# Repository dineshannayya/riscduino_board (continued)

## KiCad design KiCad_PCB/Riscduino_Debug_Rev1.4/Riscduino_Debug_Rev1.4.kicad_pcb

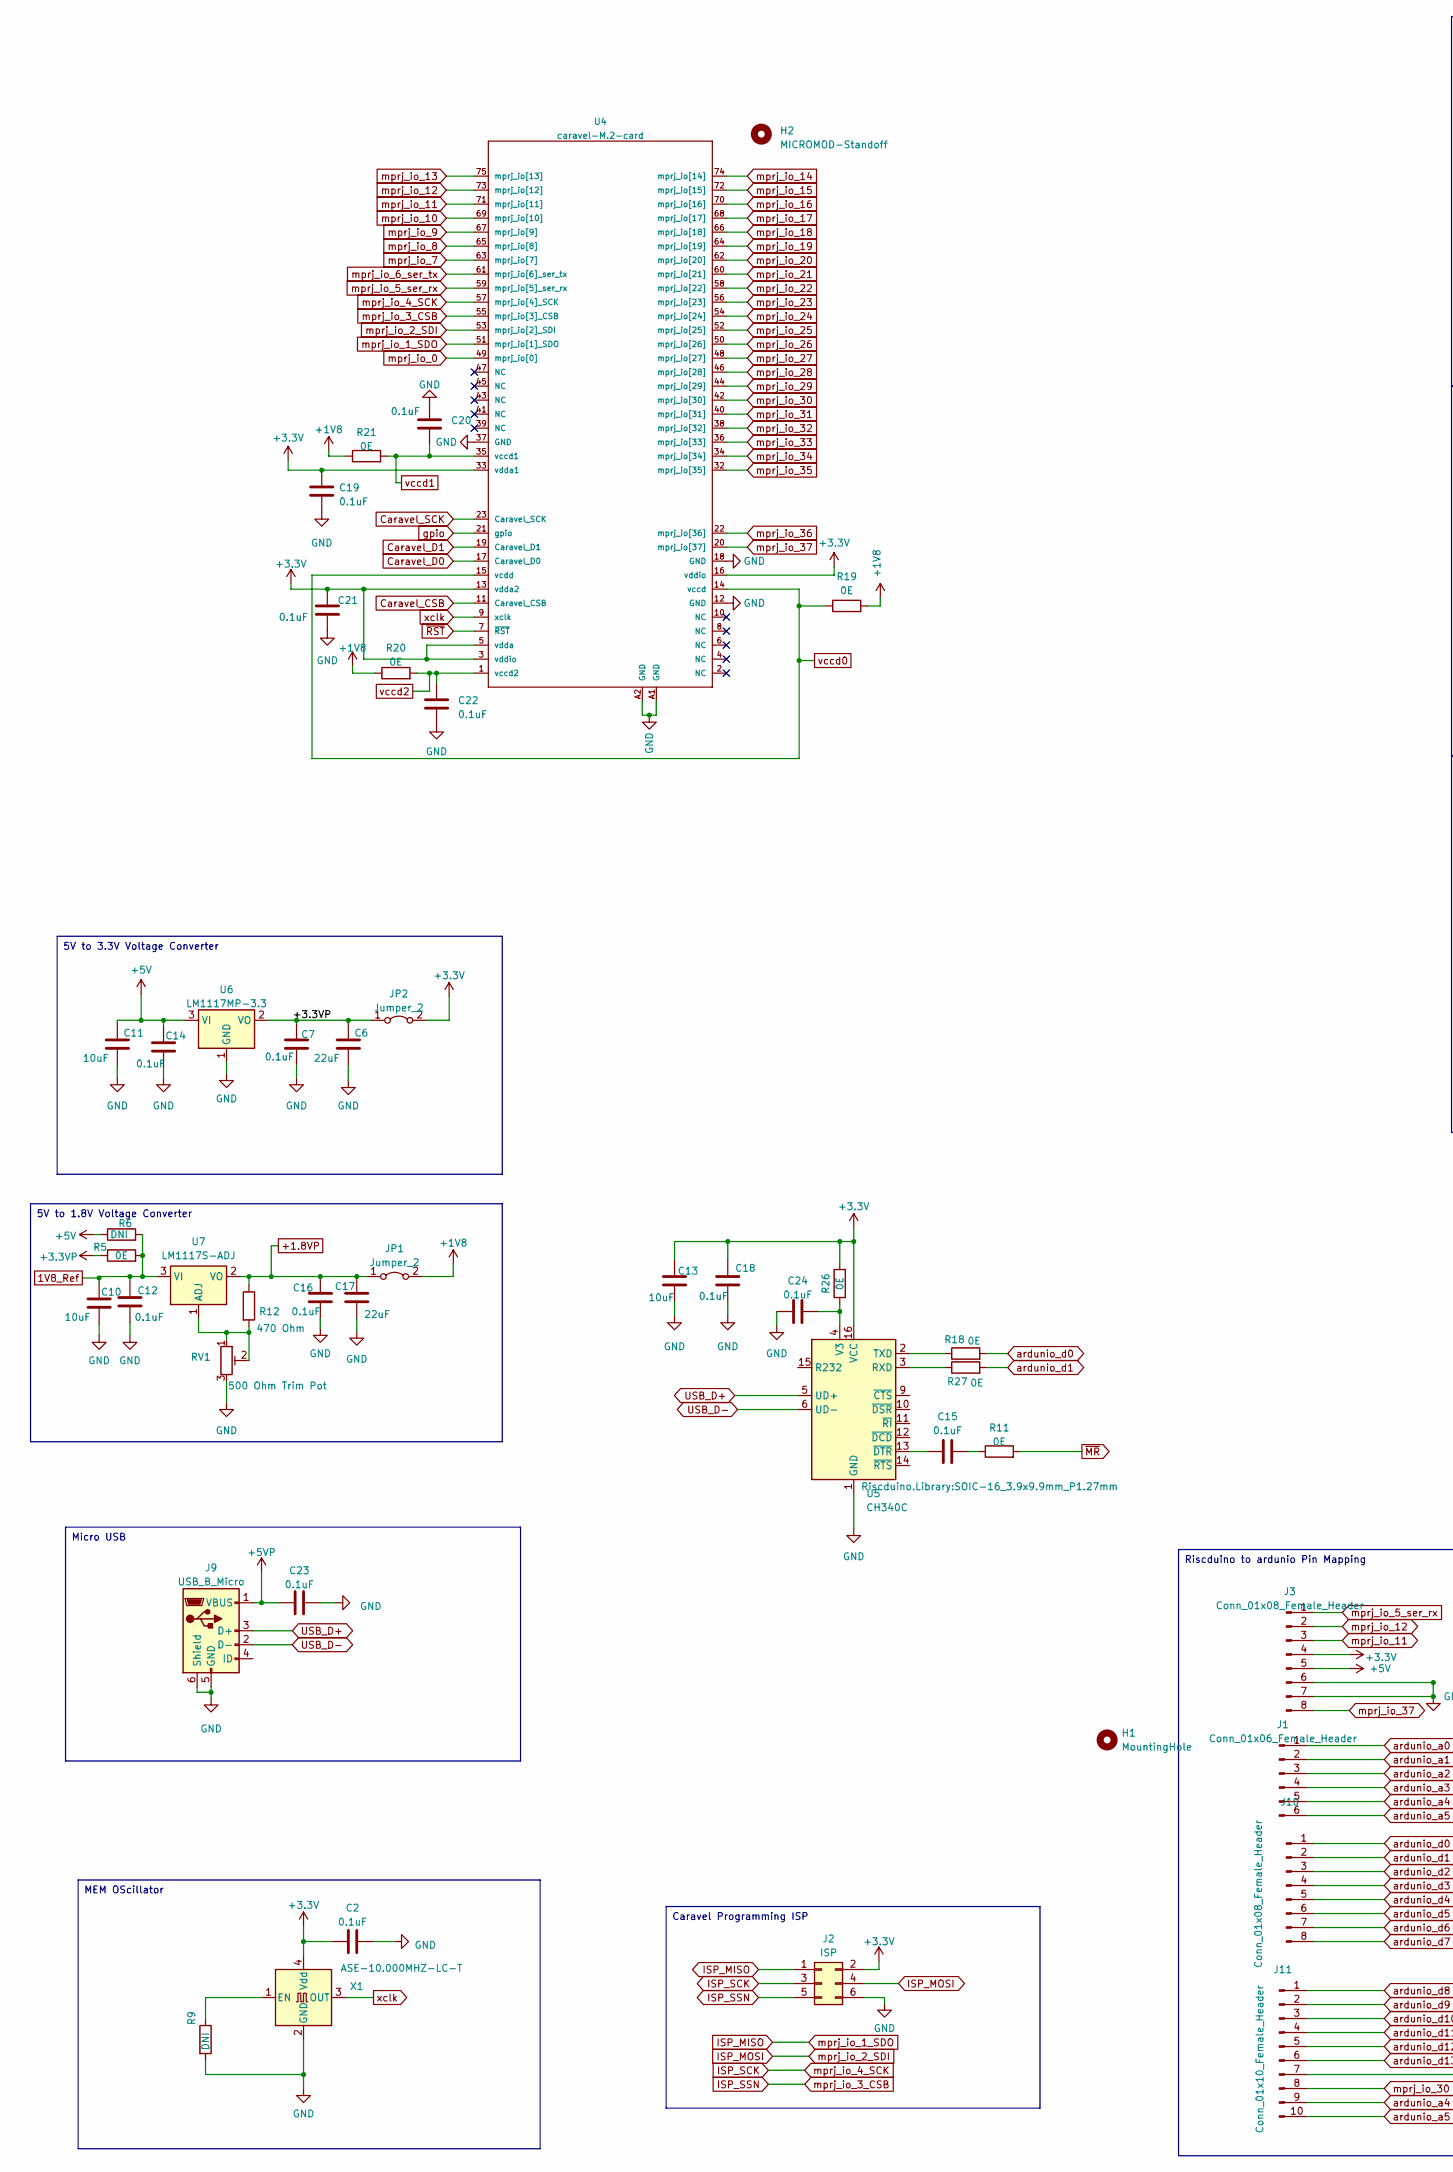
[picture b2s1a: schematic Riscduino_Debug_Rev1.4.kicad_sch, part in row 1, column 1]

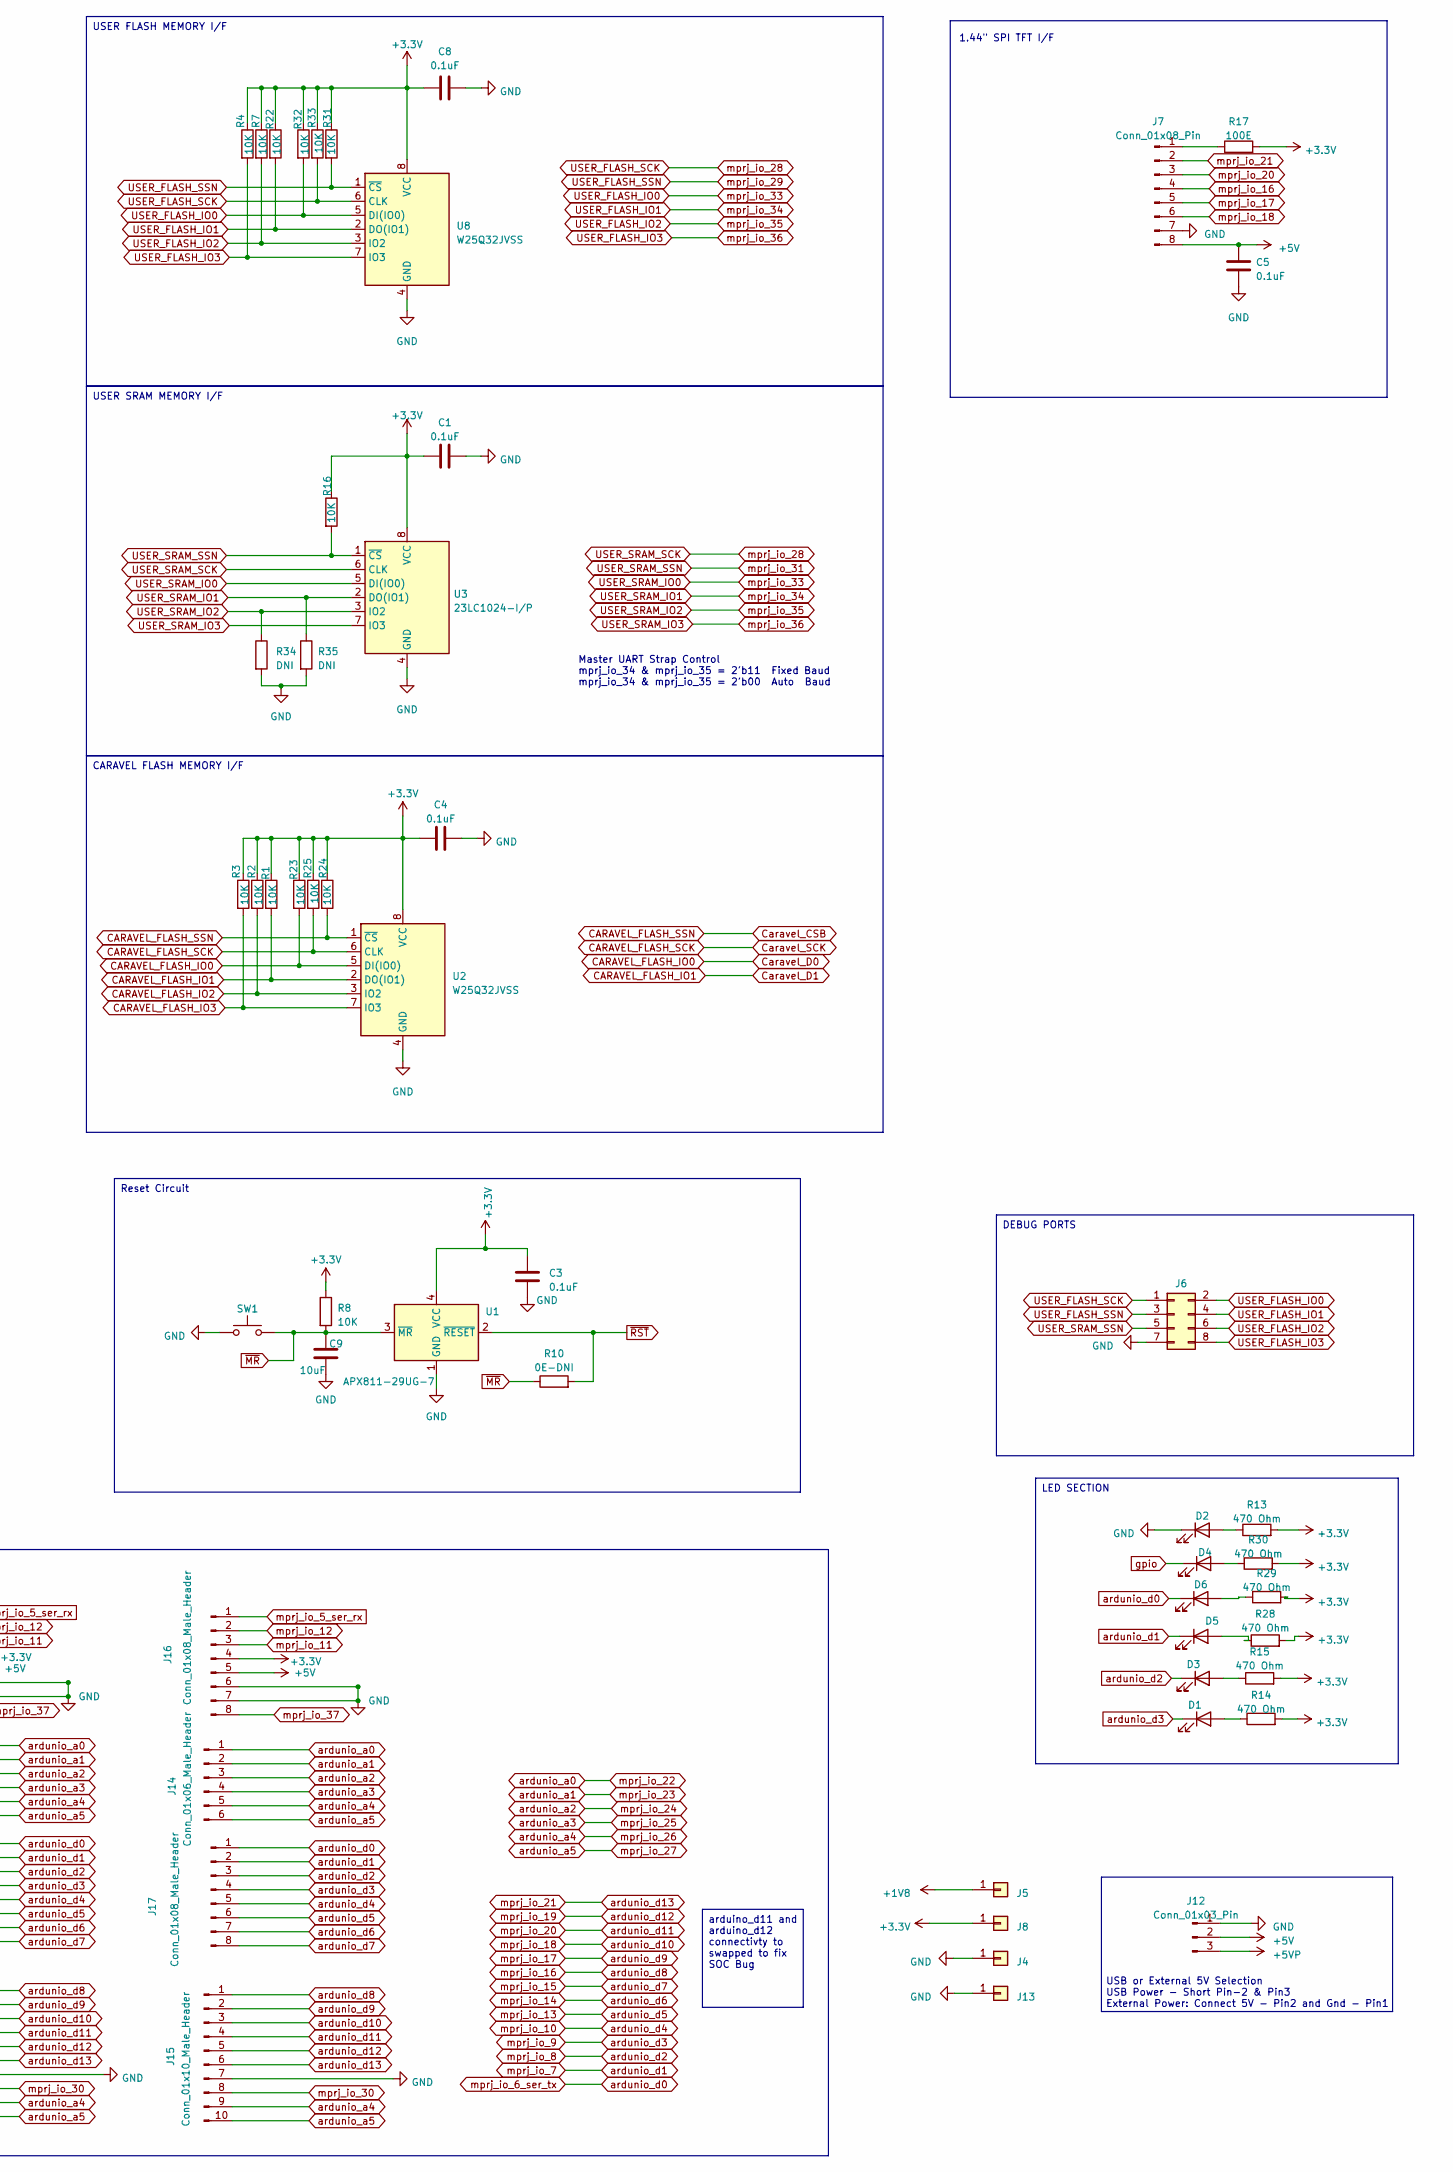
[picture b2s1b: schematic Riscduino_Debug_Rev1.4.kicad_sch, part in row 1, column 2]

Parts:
C1, C2, C3, C4, C5, C7, C8, C12, C14, C15, C16, C18, C19, C20, C21, C22, C23, C24: 0.1uF; C_0603_1608Metric_Pad1.08x0.95mm_HandSolder
C6, C17: 22uF; C_0805_2012Metric_Pad1.18x1.45mm_HandSolder
C9, C10, C11, C13: 10uF; C_0805_2012Metric_Pad1.18x1.45mm_HandSolder
D1, D2, D3, D4, D5: GREEN LED; LED_0805_2012Metric_Pad1.15x1.40mm_HandSolder
D6: BLUE LED; LED_0805_2012Metric_Pad1.15x1.40mm_HandSolder
H1: MountingHole; Arduino_UNO_R3_WithMountingHoles
H2: MICROMOD-Standoff; MicroMod-Standoff
J1: Conn_01x06_Female_Header; PinHeader_1x06_P2.54mm_Vertical
J2: ISP; PinHeader_2x03_P2.54mm_Vertical
J3, J10: Conn_01x08_Female_Header; PinHeader_1x08_P2.54mm_Vertical
J4, J5, J8, J13: Conn_01x01; PinHeader_1x01_P2.54mm_Vertical
J6: Conn_02x04_Odd_Even; PinHeader_2x04_P2.54mm_Vertical
J7: Conn_01x08_Pin; PinHeader_1x08_P2.54mm_Vertical
J9: USB_B_Micro; USB_Micro-B_Molex-105017-0001
J11: Conn_01x10_Female_Header; PinHeader_1x10_P2.54mm_Vertical
J12: Conn_01x03_Pin; PinHeader_1x03_P2.54mm_Vertical
J14: Conn_01x06_Male_Header; PinHeader_1x06_P2.54mm_Vertical
J15: Conn_01x10_Male_Header; PinHeader_1x10_P2.54mm_Vertical
J16, J17: Conn_01x08_Male_Header; PinHeader_1x08_P2.54mm_Vertical
JP1, JP2: Jumper_2; PinHeader_1x02_P2.54mm_Vertical
R1, R2, R3, R4, R7, R8, R16, R22, R23, R24, R25, R31, R32, R33: 10K; R_0603_1608Metric_Pad0.98x0.95mm_HandSolder
R5, R11, R18, R19, R20, R21, R26, R27: 0E; R_0603_1608Metric_Pad0.98x0.95mm_HandSolder
R6, R9, R34, R35: DNI; R_0603_1608Metric_Pad0.98x0.95mm_HandSolder
R10: 0E-DNI; C_0603_1608Metric_Pad1.08x0.95mm_HandSolder
R12, R13, R14, R15, R28, R29, R30: 470 Ohm; R_0603_1608Metric_Pad0.98x0.95mm_HandSolder
R17: 100E; R_0603_1608Metric_Pad0.98x0.95mm_HandSolder
RV1: 500 Ohm Trim Pot; Potentiometer_Bourns_3296W_Vertical
SW1: 4Pin Round Button SPST Straight Tactile Switch SM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; SW_SPST_EVPBF_TS4550TP
U1: APX811-29UG-7; SOT-143_Handsoldering
U2, U8: W25Q32JVSS; SOIC-8_5.23x5.23mm_P1.27mm
U3: 23LC1024-I/P; DIP-8_W7.62mm_LongPads
U4: caravel-M.2-card; M.2-CONNECTOR-E
U5: CH340C; SOIC-16_3.9x9.9mm_P1.27mm
U6: LM1117MP-3.3; SOT-223-3_TabPin2
U7: LM1117S-ADJ; SOT-223-3_TabPin2
X1: ASE-10.000MHZ-LC-T; Crystal_SMD_Abracon_ABM8G-4Pin_3.2x2.5mm

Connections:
1V8_Ref: C10.1, C12.1, R5.2, R6.2, U7.3 (VI)
+1.8VP: C16.1, C17.1, JP1.1 (A), R12.1, U7.2 (VO)
+1V8: J5.1, JP1.2 (B), R19.2, R20.1, R21.1
+3.3V: C1.1, C2.1, C3.1, C4.1, C8.1, C13.1, C18.1, C19.1, C21.1, J2.2, J3.4, J8.1, J16.4, JP2.2 (B), R1.1, R2.1, R3.1, R4.1, R7.1, R8.1, R13.2, R14.2, R15.2, R16.1, R17.2, R22.1, R23.1, R24.1, R25.1, R26.2, R28.2, R29.2, R30.2, R31.1, R32.1, R33.1, U1.4 (VCC), U2.8 (VCC), U3.8 (VCC), U4.3 (vddio), U4.5 (vdda), U4.13 (vdda2), U4.16 (vddio), U4.33 (vdda1), U5.16 (VCC), U8.8 (VCC), X1.4 (Vdd)
+3.3VP: C6.1, C7.1, JP2.1 (A), R5.1, U6.2 (VO)
+5V: C5.1, C11.1, C14.1, J3.5, J7.8, J12.2, J16.5, R6.1, U6.3 (VI)
+5VP: C23.1, J9.1 (VBUS), J12.3
CARAVEL_FLASH_IO0: R23.2, U2.5 (DI(IO0)), U4.17 (Caravel_D0)
CARAVEL_FLASH_IO1: R1.2, U2.2 (DO(IO1)), U4.19 (Caravel_D1)
CARAVEL_FLASH_IO2: R2.2, U2.3 (IO2)
CARAVEL_FLASH_IO3: R3.2, U2.7 (IO3)
CARAVEL_FLASH_SCK: R25.2, U2.6 (CLK), U4.23 (Caravel_SCK)
CARAVEL_FLASH_SSN: R24.2, U2.1 (~CS), U4.11 (Caravel_CSB)
GND: C1.2, C2.2, C3.2, C4.2, C5.2, C6.2, C7.2, C8.2, C9.2, C10.2, C11.2, C12.2, C13.2, C14.2, C16.2, C17.2, C18.2, C19.2, C20.1, C21.2, C22.2, C23.2, C24.1, D2.1 (K), J2.6, J3.6, J3.7, J4.1, J6.7, J7.7, J9.5 (GND), J9.6 (Shield), J11.7, J12.1, J13.1, J15.7, J16.6, J16.7, R9.2, R34.2, R35.2, RV1.3, SW1.1, U1.1 (GND), U2.4 (GND), U3.4 (GND), U4.12 (GND), U4.18 (GND), U4.37 (GND), U4.A1 (GND), U4.A2 (GND), U5.1 (GND), U6.1 (GND), U8.4 (GND), X1.2 (GND)
ISP_MISO: J2.1, U4.51 (mprj_io[1]_SDO)
ISP_MOSI: J2.4, U4.53 (mprj_io[2]_SDI)
ISP_SCK: J2.3, U4.57 (mprj_io[4]_SCK)
ISP_SSN: J2.5, U4.55 (mprj_io[3]_CSB)
unnamed: C15.2, R11.1
unnamed 19: D1.2 (A), R14.1; also elsewhere on the board
unnamed: D2.2 (A), R13.1
unnamed: D3.2 (A), R15.1
unnamed: D4.2 (A), R30.1
unnamed: D5.2 (A), R28.1
unnamed: D6.2 (A), R29.1
unnamed: J7.1, R17.1
unnamed: R27.1, U5.3 (RXD)
unnamed: R18.1, U5.2 (TXD)
unnamed: C24.2, R26.1, U5.4 (V3)
unnamed: C15.1, U5.13 (~DTR)
unnamed: R12.2, RV1.1, RV1.2, U7.1 (ADJ)
unnamed: R9.1, X1.1 (EN)
USB_D+: J9.3 (D+), U5.5 (UD+)
USB_D-: J9.2 (D-), U5.6 (UD-)
USER_FLASH_IO0: J6.2, R32.2, U3.5 (DI(IO0)), U4.36 (mprj_io[33]), U8.5 (DI(IO0))
USER_FLASH_IO1: J6.4, R22.2, R35.1, U3.2 (DO(IO1)), U4.34 (mprj_io[34]), U8.2 (DO(IO1))
USER_FLASH_IO2: J6.6, R7.2, R34.1, U3.3 (IO2), U4.32 (mprj_io[35]), U8.3 (IO2)
USER_FLASH_IO3: J6.8, R4.2, U3.7 (IO3), U4.22 (mprj_io[36]), U8.7 (IO3)
USER_FLASH_SCK: J6.1, R33.2, U3.6 (CLK), U4.46 (mprj_io[28]), U8.6 (CLK)
USER_FLASH_SSN: J6.3, R31.2, U4.44 (mprj_io[29]), U8.1 (~CS)
USER_SRAM_SSN: J6.5, R16.2, U3.1 (~CS), U4.40 (mprj_io[31])
ardunio_a0: J1.1, J14.1, U4.58 (mprj_io[22])
ardunio_a1: J1.2, J14.2, U4.56 (mprj_io[23])
ardunio_a2: J1.3, J14.3, U4.54 (mprj_io[24])
ardunio_a3: J1.4, J14.4, U4.52 (mprj_io[25])
ardunio_a4: J1.5, J11.9, J14.5, J15.9, U4.50 (mprj_io[26])
ardunio_a5: J1.6, J11.10, J14.6, J15.10, U4.48 (mprj_io[27])
ardunio_d0: D6.1 (K), J10.1, J17.1, R18.2, U4.61 (mprj_io[6]_ser_tx)
ardunio_d1: D5.1 (K), J10.2, J17.2, R27.2, U4.63 (mprj_io[7])
ardunio_d2: D3.1 (K), J10.3, J17.3, U4.65 (mprj_io[8])
ardunio_d3: D1.1 (K), J10.4, J17.4, U4.67 (mprj_io[9]), U8.67; also elsewhere on the board
ardunio_d4: J10.5, J17.5, U4.69 (mprj_io[10])
ardunio_d5: J10.6, J17.6, U4.75 (mprj_io[13])
ardunio_d6: J10.7, J17.7, U4.74 (mprj_io[14])
ardunio_d7: J10.8, J17.8, U4.72 (mprj_io[15])
ardunio_d8: J7.4, J11.1, J15.1, U4.70 (mprj_io[16])
ardunio_d9: J7.5, J11.2, J15.2, U4.68 (mprj_io[17])
ardunio_d10: J7.6, J11.3, J15.3, U4.66 (mprj_io[18])
ardunio_d11: J7.3, J11.4, J15.4, U4.62 (mprj_io[20])
ardunio_d12: J11.5, J15.5, U4.64 (mprj_io[19])
ardunio_d13: J7.2, J11.6, J15.6, U4.60 (mprj_io[21])
gpio: D4.1 (K), U4.21 (gpio)
mprj_io_0: U4.49 (mprj_io[0])
mprj_io_5_ser_rx: J3.1, J16.1, U4.59 (mprj_io[5]_ser_rx)
mprj_io_11: J3.3, J16.3, U4.71 (mprj_io[11])
mprj_io_12: J3.2, J16.2, U4.73 (mprj_io[12])
mprj_io_30: J11.8, J15.8, U4.42 (mprj_io[30])
mprj_io_32: U4.38 (mprj_io[32])
mprj_io_37: J3.8, J16.8, U4.20 (mprj_io[37])
vccd0: R19.1, U4.14 (vccd), U4.15 (vcdd)
vccd1: C20.2, R21.2, U4.35 (vccd1)
vccd2: C22.1, R20.2, U4.1 (vccd2)
xclk: U4.9 (xclk), X1.3 (OUT)
~MR: C9.1, R8.2, R10.1, R11.2, SW1.2, U1.3 (~MR)
~RST: R10.2, U1.2 (~RESET), U4.7 (~RST)

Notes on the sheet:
MEM OScillator
5V to 3.3V Voltage Converter
LED SECTION
Riscduino to ardunio Pin Mapping
Micro USB
arduino_d11 and arduino_d12 connectivty to swapped to fix SOC Bug
USER SRAM MEMORY I/F
DEBUG PORTS
Caravel Programming ISP
USER FLASH MEMORY I/F
5V to 1.8V Voltage Converter
Reset Circuit
CARAVEL FLASH MEMORY I/F
USB or External 5V Selection USB Power - Short Pin-2 & Pin3 External Power: Connect 5V - Pin2 and Gnd - Pin1
1.44" SPI TFT I/F
Master UART Strap Control mprj_io_34 & mprj_io_35 = 2'b11 Fixed Baud mprj_io_34 & mprj_io_35 = 2'b00 Auto Baud

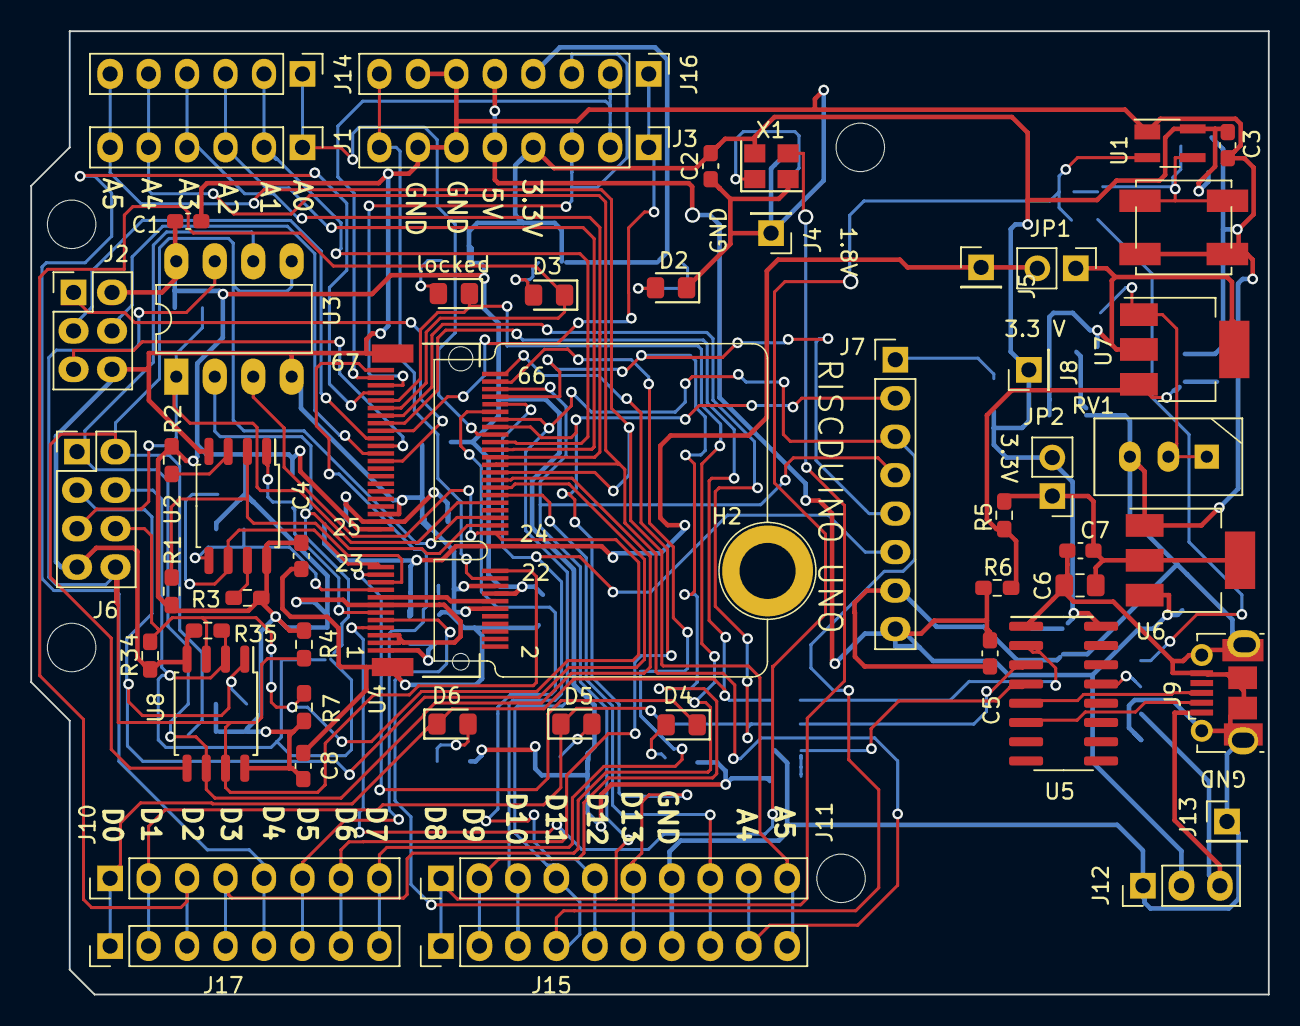
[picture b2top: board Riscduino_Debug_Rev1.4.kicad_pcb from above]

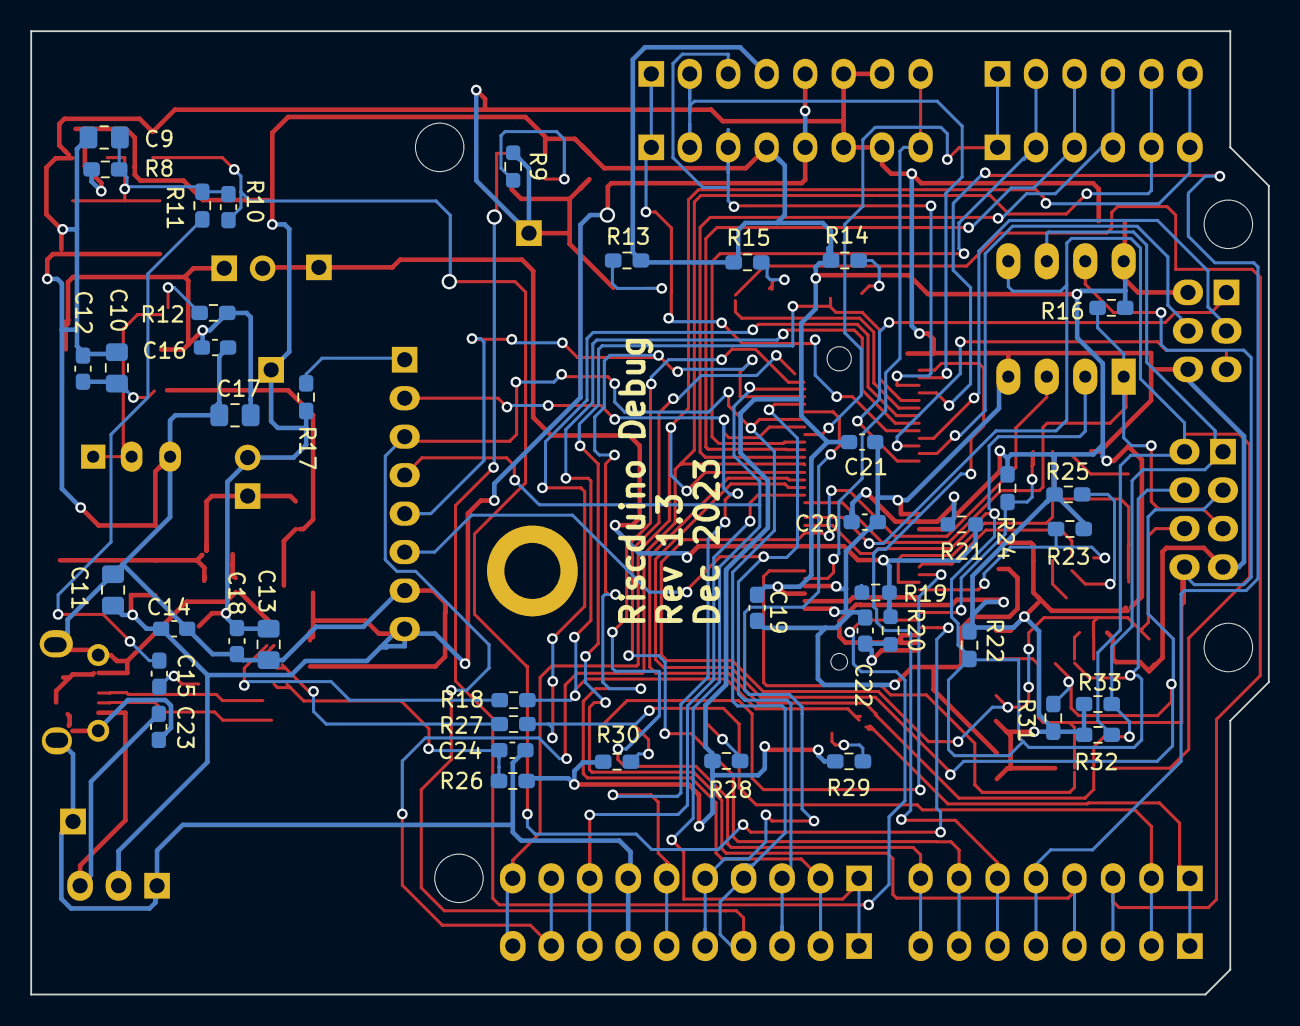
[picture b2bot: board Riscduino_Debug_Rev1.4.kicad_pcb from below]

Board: 2 copper layers, 81.7 x 63.6 mm, 97 parts (42 on the bottom side), 73 nets.

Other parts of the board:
locked: GREEN LED; LED_0805_2012Metric_Pad1.15x1.40mm_HandSolder

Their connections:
unnamed 19: locked.2 (A); also elsewhere on the board
ardunio_d3: locked.1 (K); also elsewhere on the board

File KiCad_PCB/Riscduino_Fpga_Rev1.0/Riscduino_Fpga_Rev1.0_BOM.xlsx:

Id | Designator | Footprint | Quantity | Designation | Supplier and ref | Column1 | _1
1 | J20 | USB_A_Molex_67643_Horizontal | 1 | USB Type A Female
2 | J19 | PinHeader_2x04_P2.54mm_Vertical | 1 | Conn_02x04_Male_Header
3 | SW2 | DIP-8_W7.62mm | 1 | SW_DIP_x04
4 | J18,J5 | PinHeader_2x15_P2.54mm_Vertical | 2 | Conn_02x15_Male_Header
5 | J4,J13,J8 | PinHeader_1x01_P2.54mm_Vertical | 3 | Conn_01x01
6 | U6 | SOT-223-3_TabPin2 | 1 | LM1117MP-3.3
7 | U8 | SOIC-8_5.23x5.23mm_P1.27mm | 1 | W25Q32JVSS
8 | J3,J10,J7 | PinHeader_1x08_P2.54mm_Vertical | 3 | Conn_01x08_Female_Header
9 | U5 | SOIC-16_3.9x9.9mm_P1.27mm | 1 | CH340C
10 | J6 | PinHeader_2x04_P2.54mm_Vertical | 1 | Conn_02x04_Male_Header
11 | C2,C8,C3,C5,C24,C7,C18,C1,C15,C14 | C_0603_1608Metric_Pad1.08x0.95mm_HandSolder | 10 | 0.1uF
12 | R25,R23,R21,R20,R24,R4,R36,R7,R5,R8,R19,R22,R31,R6,R32,R33,R16,R12 | R_0603_1608Metric_Pad0.98x0.95mm_HandSolder | 18 | 10K
13 | C23,C17,C16,C12,C4,C10 | C_0603_1608Metric_Pad1.08x0.95mm_HandSolder | 6 | 0.1uF
14 | C6 | C_0805_2012Metric_Pad1.18x1.45mm_HandSolder | 1 | 22uF
15 | J1 | PinHeader_1x06_P2.54mm_Vertical | 1 | Conn_01x06_Female_Header
16 | D2,D4 | LED_0805_2012Metric_Pad1.15x1.40mm_HandSolder | 2 | GREEN LED
17 | SW3,SW5,SW8,SW6,SW4,SW1,SW7 | SW_SPST_EVPBF_TS4550TP | 7 | 4Pin Round Button SPST Straight Tactile Switch SMD - TS4550TP
18 | D3,D1,D5,D6 | LED_0805_2012Metric_Pad1.15x1.40mm_HandSolder | 4 | BLUE LED
19 | J14 | PinHeader_1x06_P2.54mm_Vertical | 1 | Conn_01x06_Male_Header
20 | R26,R11,R3,R1 | R_0603_1608Metric_Pad0.98x0.95mm_HandSolder | 4 | 0E
21 | J16,J17 | PinHeader_1x08_P2.54mm_Vertical | 2 | Conn_01x08_Male_Header
22 | R27,R18 | R_0603_1608Metric_Pad0.98x0.95mm_HandSolder | 2 | 0E
23 | J9,J21 | USB_Micro-B_Molex-105017-0001 | 2 | USB_B_Micro_Female
24 | R34,R35 | R_0603_1608Metric_Pad0.98x0.95mm_HandSolder | 2 | DNI
25 | J15 | PinHeader_1x10_P2.54mm_Vertical | 1 | Conn_01x10_Male_Header
26 | H1 | Arduino_UNO_R3_WithMountingHoles | 1 | MountingHole
27 | J11 | PinHeader_1x10_P2.54mm_Vertical | 1 | Conn_01x10_Female_Header
28 | U3 | DIP-8_W7.62mm_LongPads | 1 | 23LC1024-I/P
29 | U1 | SOT-143_Handsoldering | 1 | APX811-29UG-7
30 | J12,J2 | PinHeader_1x03_P2.54mm_Vertical | 2 | Conn_01x03_Male_Header
31 | X1 | Crystal_SMD_Abracon_ABM8G-4Pin_3.2x2.5mm | 1 | ASE-10.000MHZ-LC-T
32 | R13,R29,R28,R14,R15,R30 | R_0603_1608Metric_Pad0.98x0.95mm_HandSolder | 6 | 470 Ohm
33 | R17 | R_0603_1608Metric_Pad0.98x0.95mm_HandSolder | 1 | 100E
34 | C13,C11 | C_0805_2012Metric_Pad1.18x1.45mm_HandSolder | 2 | 10uF
35 | R9 | R_0603_1608Metric_Pad0.98x0.95mm_HandSolder | 1 | DNI
36 | R2 | R_0603_1608Metric_Pad0.98x0.95mm_HandSolder | 1 | DNI-0E
